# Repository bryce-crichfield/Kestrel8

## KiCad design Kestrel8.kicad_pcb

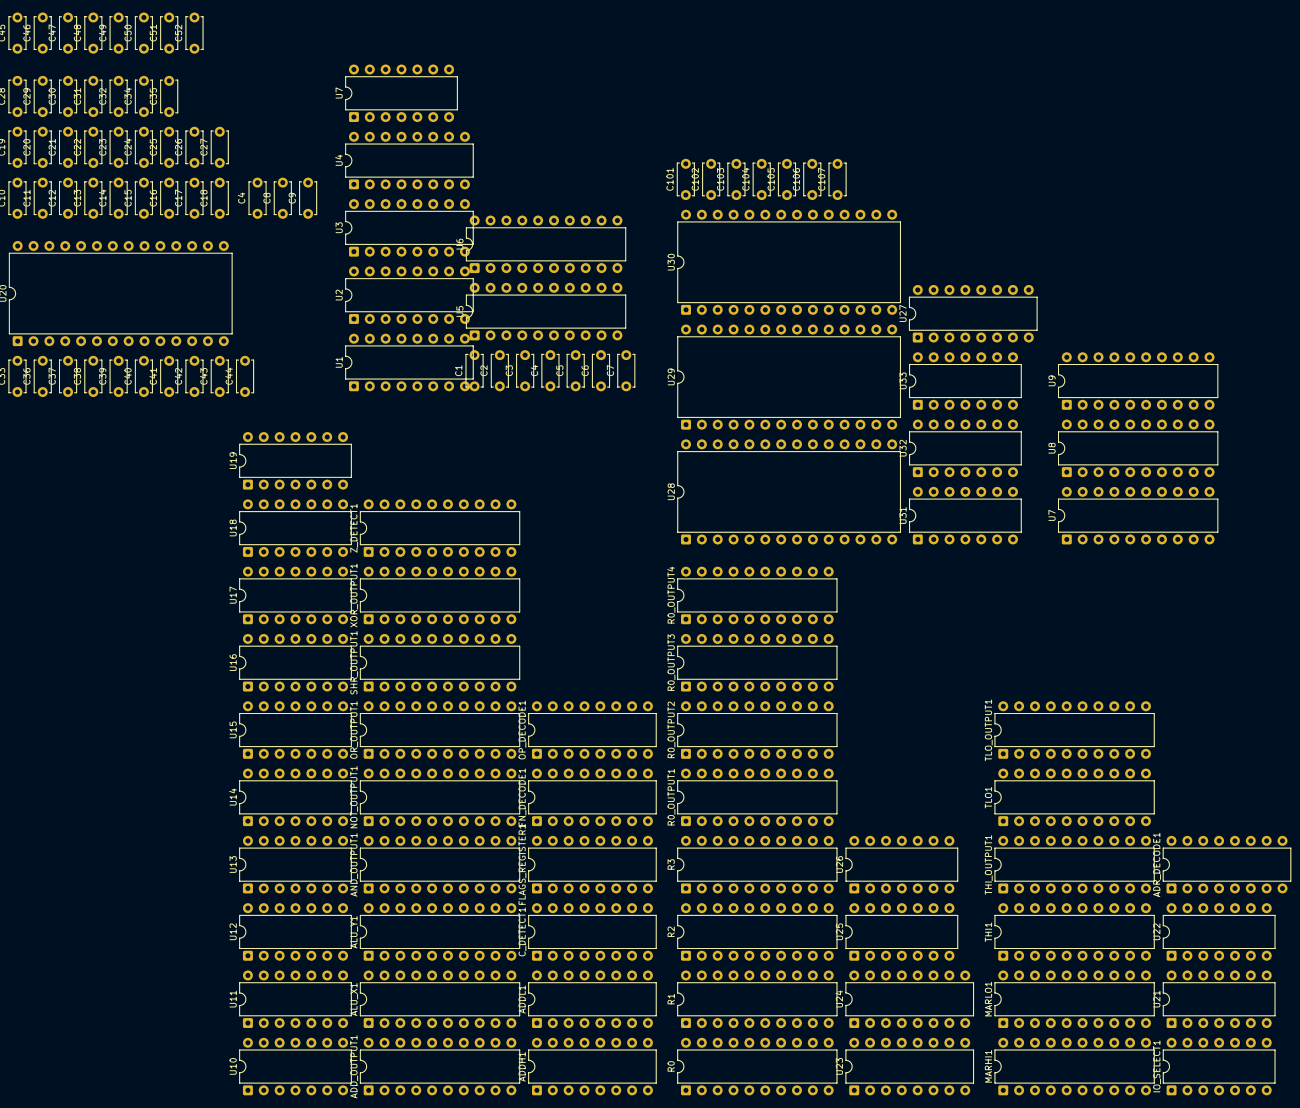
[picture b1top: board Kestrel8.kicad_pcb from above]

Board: 2 copper layers, 125 parts (0 on the bottom side), 249 nets, no tracks yet.

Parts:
ADDH1: 74LS283; DIP-16_W7.62mm
ADDL1: 74LS283; DIP-16_W7.62mm
ADD_OUTPUT1: 74LS541; DIP-20_W7.62mm
ADR_DECODE1: 74LS138; DIP-16_W7.62mm
ALU_X1: 74LS377; DIP-20_W7.62mm
ALU_Y1: 74LS377; DIP-20_W7.62mm
AND_OUTPUT1: 74LS541; DIP-20_W7.62mm
C1, C2, C3, C4, C4#2, C5, C6, C7, C8, C9, C10, C11, C12, C13, C14, C15, C16, C17, C18, C19, C20, C21, C22, C23, C24, C25, C26, C27, C28, C29, C30, C31, C32, C33, C34, C35, C36, C37, C38, C39, C40, C41, C42, C43, C44, C45, C46, C47, C48, C49, C50, C51, C52, C101, C102, C103, C104, C105, C106, C107: 100nF; C_Disc_D5.0mm_W2.5mm_P5.00mm
C_DETECT1: 74HC151; DIP-16_W7.62mm
FLAGS_REGISTER1: 74LS173; DIP-16_W7.62mm
FN_DECODE1: 74LS138; DIP-16_W7.62mm
IO_SELECT1: 74LS30; DIP-14_W7.62mm
MARHI1: 74LS377; DIP-20_W7.62mm
MARLO1: 74LS377; DIP-20_W7.62mm
NOT_OUTPUT1: 74LS540; DIP-20_W7.62mm
OP_DECODE1: 74LS157; DIP-16_W7.62mm
OR_OUTPUT1: 74LS541; DIP-20_W7.62mm
R0, R1, R2, R3: 74LS377; DIP-20_W7.62mm
R0_OUTPUT1, R0_OUTPUT2, R0_OUTPUT3, R0_OUTPUT4: 74LS541; DIP-20_W7.62mm
SHR_OUTPUT1: 74LS541; DIP-20_W7.62mm
THI1: 74LS377; DIP-20_W7.62mm
THI_OUTPUT1: 74HC541; DIP-20_W7.62mm
TLO1: 74LS377; DIP-20_W7.62mm
TLO_OUTPUT1: 74HC541; DIP-20_W7.62mm
U1, U2, U3, U4, U27: 74LS163; DIP-16_W7.62mm
U5, U6, U9: 74LS541; DIP-20_W7.62mm
U7, U8: 74LS377; DIP-20_W7.62mm
U7#2: 74LS04; DIP-14_W7.62mm
U10, U14, U17, U18: 74LS86; DIP-14_W7.62mm
U11: 74HC00; DIP-14_W7.62mm
U12, U15, U25, U31: 74LS08; DIP-14_W7.62mm
U13, U16: 74HC32; DIP-14_W7.62mm
U19: 74LS11; DIP-14_W7.62mm
U20: CY62256-70PC; DIP-28_W15.24mm
U21: 74LS30; DIP-14_W7.62mm
U22, U32: 74LS32; DIP-14_W7.62mm
U23, U24: 74LS139; DIP-16_W7.62mm
U26: 74LS00; DIP-14_W7.62mm
U28, U29, U30: AT28C64B; DIP-28_W15.24mm
U33: 74LS74; DIP-14_W7.62mm
XOR_OUTPUT1: 74LS541; DIP-20_W7.62mm
Z_DETECT1: 74LS688; DIP-20_W7.62mm

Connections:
/ControlUnit/SC_0: U27.14 (Q0), U28.10 (A0), U29.10 (A0), U30.10 (A0)
/ControlUnit/SC_1: U27.13 (Q1), U28.9 (A1), U29.9 (A1), U30.9 (A1)
/ControlUnit/SC_2: U27.12 (Q2), U28.8 (A2), U29.8 (A2), U30.8 (A2)
/ControlUnit/SC_3: U27.11 (Q3), U28.7 (A3), U29.7 (A3), U30.7 (A3)
/ControlUnit//HALT_SET: U32.3, U33.4 (~S)
/ControlUnit//SC_MR: U27.1 (~MR), U31.3
/ProgramCounter/PC_RIPPLE_1: U1.15 (TC), U2.10 (CET)
/ProgramCounter/PC_RIPPLE_2: U2.15 (TC), U3.10 (CET)
/ProgramCounter/PC_RIPPLE_3: U3.15 (TC), U4.10 (CET)
/ProgramCounter/Q_0: U1.14 (Q0), U5.2 (A0)
/ProgramCounter/Q_1: U1.13 (Q1), U5.3 (A1)
/ProgramCounter/Q_2: U1.12 (Q2), U5.4 (A2)
/ProgramCounter/Q_3: U1.11 (Q3), U5.5 (A3)
/ProgramCounter/Q_4: U2.14 (Q0), U5.6 (A4)
/ProgramCounter/Q_5: U2.13 (Q1), U5.7 (A5)
/ProgramCounter/Q_6: U2.12 (Q2), U5.8 (A6)
/ProgramCounter/Q_7: U2.11 (Q3), U5.9 (A7)
/ProgramCounter/Q_8: U3.14 (Q0), U6.2 (A0)
/ProgramCounter/Q_9: U3.13 (Q1), U6.3 (A1)
/ProgramCounter/Q_10: U3.12 (Q2), U6.4 (A2)
/ProgramCounter/Q_11: U3.11 (Q3), U6.5 (A3)
/ProgramCounter/Q_12: U4.14 (Q0), U6.6 (A4)
/ProgramCounter/Q_13: U4.13 (Q1), U6.7 (A5)
/ProgramCounter/Q_14: U4.12 (Q2), U6.8 (A6)
/ProgramCounter/Q_15: U4.11 (Q3), U6.9 (A7)
/RegisterFile/RD_IN: U26.3, U26.4
/RegisterFile//R0_RA: U23.12 (O0), U25.1
/RegisterFile//R0_RB: U24.4 (O0), U25.2
/RegisterFile//R1_RA: U23.11 (O1), U25.4
/RegisterFile//R1_RB: U24.5 (O1), U25.5
/RegisterFile//R2_RA: U23.10 (O2), U25.9
/RegisterFile//R2_RB: U24.6 (O2), U25.10
/RegisterFile//R3_RA: U23.9 (O3), U25.12
/RegisterFile//R3_RB: U24.7 (O3), U25.13
/RegisterFile//RD_IN_GATED: U23.1 (E), U26.6
ADDH_C: ADDH1.9 (C4), C_DETECT1.4 (I0), U11.9, U11.10
ADDL_C: ADDH1.7 (C0), ADDL1.9 (C4)
ADD_0: ADDL1.4 (S1), ADD_OUTPUT1.2 (A0)
ADD_1: ADDL1.1 (S2), ADD_OUTPUT1.3 (A1)
ADD_2: ADDL1.13 (S3), ADD_OUTPUT1.4 (A2)
ADD_3: ADDL1.10 (S4), ADD_OUTPUT1.5 (A3)
ADD_4: ADDH1.4 (S1), ADD_OUTPUT1.6 (A4)
ADD_5: ADDH1.1 (S2), ADD_OUTPUT1.7 (A5)
ADD_6: ADDH1.13 (S3), ADD_OUTPUT1.8 (A6)
ADD_7: ADDH1.10 (S4), ADD_OUTPUT1.9 (A7)
ADR_0: MARLO1.3 (D0), TLO_OUTPUT1.18 (Y0), U1.3 (D0), U5.18 (Y0)
ADR_1: MARLO1.4 (D1), TLO_OUTPUT1.17 (Y1), U1.4 (D1), U5.17 (Y1)
ADR_2: MARLO1.7 (D2), TLO_OUTPUT1.16 (Y2), U1.5 (D2), U5.16 (Y2)
ADR_3: MARLO1.8 (D3), TLO_OUTPUT1.15 (Y3), U1.6 (D3), U5.15 (Y3)
ADR_4: MARLO1.13 (D4), TLO_OUTPUT1.14 (Y4), U2.3 (D0), U5.14 (Y4)
ADR_5: MARLO1.14 (D5), TLO_OUTPUT1.13 (Y5), U2.4 (D1), U5.13 (Y5)
ADR_6: MARLO1.17 (D6), TLO_OUTPUT1.12 (Y6), U2.5 (D2), U5.12 (Y6)
ADR_7: MARLO1.18 (D7), TLO_OUTPUT1.11 (Y7), U2.6 (D3), U5.11 (Y7)
ADR_8: MARHI1.3 (D0), THI_OUTPUT1.18 (Y0), U3.3 (D0), U6.18 (Y0)
ADR_9: MARHI1.4 (D1), THI_OUTPUT1.17 (Y1), U3.4 (D1), U6.17 (Y1)
ADR_10: MARHI1.7 (D2), THI_OUTPUT1.16 (Y2), U3.5 (D2), U6.16 (Y2)
ADR_11: MARHI1.8 (D3), THI_OUTPUT1.15 (Y3), U3.6 (D3), U6.15 (Y3)
ADR_12: MARHI1.13 (D4), THI_OUTPUT1.14 (Y4), U4.3 (D0), U6.14 (Y4)
ADR_13: MARHI1.14 (D5), THI_OUTPUT1.13 (Y5), U4.4 (D1), U6.13 (Y5)
ADR_14: MARHI1.17 (D6), THI_OUTPUT1.12 (Y6), U4.5 (D2), U6.12 (Y6)
ADR_15: MARHI1.18 (D7), THI_OUTPUT1.11 (Y7), U4.6 (D3), U6.11 (Y7)
ALU_FUNC: OP_DECODE1.1 (S), U30.15 (I/O3)
ALU_OP_0: FN_DECODE1.1 (A0), OP_DECODE1.4 (Za)
ALU_OP_1: FN_DECODE1.2 (A1), OP_DECODE1.7 (Zb)
ALU_OP_2: FN_DECODE1.3 (A2), OP_DECODE1.9 (Zc)
AND_0: AND_OUTPUT1.2 (A0), U15.3
AND_1: AND_OUTPUT1.3 (A1), U15.6
AND_2: AND_OUTPUT1.4 (A2), U15.8
AND_3: AND_OUTPUT1.5 (A3), U15.11
AND_4: AND_OUTPUT1.6 (A4), U12.3
AND_5: AND_OUTPUT1.7 (A5), U12.6
AND_6: AND_OUTPUT1.8 (A6), U12.8
AND_7: AND_OUTPUT1.9 (A7), U12.11
CLK: ALU_X1.11 (CP), ALU_Y1.11 (CP), FLAGS_REGISTER1.7 (Cp), MARHI1.11 (CP), MARLO1.11 (CP), R0.11 (CP), R1.11 (CP), R2.11 (CP), R3.11 (CP), THI1.11 (CP), TLO1.11 (CP), U1.2 (CP), U2.2 (CP), U3.2 (CP), U4.2 (CP), U7.11 (CP), U8.11 (CP), U22.2, U27.2 (CP), U32.2
DAT_0: ADD_OUTPUT1.18 (Y0), ALU_X1.3 (D0), ALU_Y1.3 (D0), AND_OUTPUT1.18 (Y0), NOT_OUTPUT1.18 (Y0), OR_OUTPUT1.18 (Y0), R0.3 (D0), R0_OUTPUT1.18 (Y0), R0_OUTPUT2.18 (Y0), R0_OUTPUT3.18 (Y0), R0_OUTPUT4.18 (Y0), R1.3 (D0), R2.3 (D0), R3.3 (D0), SHR_OUTPUT1.18 (Y0), THI1.3 (D0), TLO1.3 (D0), U7.3 (D0), U8.3 (D0), U9.18 (Y0), U20.11 (Q0), XOR_OUTPUT1.18 (Y0), Z_DETECT1.2 (P0)
DAT_1: ADD_OUTPUT1.17 (Y1), ALU_X1.4 (D1), ALU_Y1.4 (D1), AND_OUTPUT1.17 (Y1), NOT_OUTPUT1.17 (Y1), OR_OUTPUT1.17 (Y1), R0.4 (D1), R0_OUTPUT1.17 (Y1), R0_OUTPUT2.17 (Y1), R0_OUTPUT3.17 (Y1), R0_OUTPUT4.17 (Y1), R1.4 (D1), R2.4 (D1), R3.4 (D1), SHR_OUTPUT1.17 (Y1), THI1.4 (D1), TLO1.4 (D1), U7.4 (D1), U8.4 (D1), U9.17 (Y1), U20.12 (Q1), XOR_OUTPUT1.17 (Y1), Z_DETECT1.4 (P1)
DAT_2: ADD_OUTPUT1.16 (Y2), ALU_X1.7 (D2), ALU_Y1.7 (D2), AND_OUTPUT1.16 (Y2), NOT_OUTPUT1.16 (Y2), OR_OUTPUT1.16 (Y2), R0.7 (D2), R0_OUTPUT1.16 (Y2), R0_OUTPUT2.16 (Y2), R0_OUTPUT3.16 (Y2), R0_OUTPUT4.16 (Y2), R1.7 (D2), R2.7 (D2), R3.7 (D2), SHR_OUTPUT1.16 (Y2), THI1.7 (D2), TLO1.7 (D2), U7.7 (D2), U8.7 (D2), U9.16 (Y2), U20.13 (Q2), XOR_OUTPUT1.16 (Y2), Z_DETECT1.6 (P2)
DAT_3: ADD_OUTPUT1.15 (Y3), ALU_X1.8 (D3), ALU_Y1.8 (D3), AND_OUTPUT1.15 (Y3), NOT_OUTPUT1.15 (Y3), OR_OUTPUT1.15 (Y3), R0.8 (D3), R0_OUTPUT1.15 (Y3), R0_OUTPUT2.15 (Y3), R0_OUTPUT3.15 (Y3), R0_OUTPUT4.15 (Y3), R1.8 (D3), R2.8 (D3), R3.8 (D3), SHR_OUTPUT1.15 (Y3), THI1.8 (D3), TLO1.8 (D3), U7.8 (D3), U8.8 (D3), U9.15 (Y3), U20.15 (Q3), XOR_OUTPUT1.15 (Y3), Z_DETECT1.8 (P3)
DAT_4: ADD_OUTPUT1.14 (Y4), ALU_X1.13 (D4), ALU_Y1.13 (D4), AND_OUTPUT1.14 (Y4), NOT_OUTPUT1.14 (Y4), OR_OUTPUT1.14 (Y4), R0.13 (D4), R0_OUTPUT1.14 (Y4), R0_OUTPUT2.14 (Y4), R0_OUTPUT3.14 (Y4), R0_OUTPUT4.14 (Y4), R1.13 (D4), R2.13 (D4), R3.13 (D4), SHR_OUTPUT1.14 (Y4), THI1.13 (D4), TLO1.13 (D4), U7.13 (D4), U8.13 (D4), U9.14 (Y4), U20.16 (Q4), XOR_OUTPUT1.14 (Y4), Z_DETECT1.11 (P4)
DAT_5: ADD_OUTPUT1.13 (Y5), ALU_X1.14 (D5), ALU_Y1.14 (D5), AND_OUTPUT1.13 (Y5), NOT_OUTPUT1.13 (Y5), OR_OUTPUT1.13 (Y5), R0.14 (D5), R0_OUTPUT1.13 (Y5), R0_OUTPUT2.13 (Y5), R0_OUTPUT3.13 (Y5), R0_OUTPUT4.13 (Y5), R1.14 (D5), R2.14 (D5), R3.14 (D5), SHR_OUTPUT1.13 (Y5), THI1.14 (D5), TLO1.14 (D5), U7.14 (D5), U8.14 (D5), U9.13 (Y5), U20.17 (Q5), XOR_OUTPUT1.13 (Y5), Z_DETECT1.13 (P5)
DAT_6: ADD_OUTPUT1.12 (Y6), ALU_X1.17 (D6), ALU_Y1.17 (D6), AND_OUTPUT1.12 (Y6), NOT_OUTPUT1.12 (Y6), OR_OUTPUT1.12 (Y6), R0.17 (D6), R0_OUTPUT1.12 (Y6), R0_OUTPUT2.12 (Y6), R0_OUTPUT3.12 (Y6), R0_OUTPUT4.12 (Y6), R1.17 (D6), R2.17 (D6), R3.17 (D6), SHR_OUTPUT1.12 (Y6), THI1.17 (D6), TLO1.17 (D6), U7.17 (D6), U8.17 (D6), U9.12 (Y6), U20.18 (Q6), XOR_OUTPUT1.12 (Y6), Z_DETECT1.15 (P6)
DAT_7: ADD_OUTPUT1.11 (Y7), ALU_X1.18 (D7), ALU_Y1.18 (D7), AND_OUTPUT1.11 (Y7), NOT_OUTPUT1.11 (Y7), OR_OUTPUT1.11 (Y7), R0.18 (D7), R0_OUTPUT1.11 (Y7), R0_OUTPUT2.11 (Y7), R0_OUTPUT3.11 (Y7), R0_OUTPUT4.11 (Y7), R1.18 (D7), R2.18 (D7), R3.18 (D7), SHR_OUTPUT1.11 (Y7), THI1.18 (D7), TLO1.18 (D7), U7.18 (D7), U8.18 (D7), U9.11 (Y7), U20.19 (Q7), XOR_OUTPUT1.11 (Y7), Z_DETECT1.17 (P7)
GND: ADDH1.8 (GND), ADDL1.8 (GND), ADD_OUTPUT1.1 (G1), ADD_OUTPUT1.10 (GND), ADR_DECODE1.5 (E2), ADR_DECODE1.8 (GND), ALU_X1.10 (GND), ALU_Y1.10 (GND), AND_OUTPUT1.1 (G1), AND_OUTPUT1.10 (GND), C1.2, C2.2, C3.2, C4.2, C4#2.2, C5.2, C6.2, C7.2, C8.2, C9.2, C10.2, C11.2, C12.2, C13.2, C14.2, C15.2, C16.2, C17.2, C18.2, C19.2, C20.2, C21.2, C22.2, C23.2, C24.2, C25.2, C26.2, C27.2, C28.2, C29.2, C30.2, C31.2, C32.2, C33.2, C34.2, C35.2, C36.2, C37.2, C38.2, C39.2, C40.2, C41.2, C42.2, C43.2, C44.2, C45.2, C46.2, C47.2, C48.2, C49.2, C50.2, C51.2, C52.2, C101.2, C102.2, C103.2, C104.2, C105.2, C106.2, C107.2, C_DETECT1.1 (I3), C_DETECT1.2 (I2), C_DETECT1.7 (~E), C_DETECT1.8 (GND), C_DETECT1.14 (I5), C_DETECT1.15 (I4), FLAGS_REGISTER1.1 (Oe1), FLAGS_REGISTER1.2 (Oe2), FLAGS_REGISTER1.8 (GND), FLAGS_REGISTER1.10 (E2), FLAGS_REGISTER1.11 (D3), FLAGS_REGISTER1.12 (D2), FN_DECODE1.5 (E2), FN_DECODE1.8 (GND), MARLO1.10 (GND), NOT_OUTPUT1.1 (G1), NOT_OUTPUT1.10 (GND), OP_DECODE1.2 (I0a), OP_DECODE1.5 (I0b), OP_DECODE1.8 (GND), OP_DECODE1.11 (I0c), OP_DECODE1.13 (I1d), OP_DECODE1.14 (I0d), OP_DECODE1.15 (E), OR_OUTPUT1.1 (G1), OR_OUTPUT1.10 (GND), R0.10 (GND), R0_OUTPUT1.1 (G1), R0_OUTPUT1.10 (GND), R0_OUTPUT2.1 (G1), R0_OUTPUT2.10 (GND), R0_OUTPUT3.1 (G1), R0_OUTPUT3.10 (GND), R0_OUTPUT4.1 (G1), R0_OUTPUT4.10 (GND), R1.10 (GND), R2.10 (GND), R3.10 (GND), SHR_OUTPUT1.1 (G1), SHR_OUTPUT1.9 (A7), SHR_OUTPUT1.10 (GND), THI1.10 (GND), THI_OUTPUT1.10 (GND), TLO1.10 (GND), TLO_OUTPUT1.10 (GND), U1.8 (GND), U2.8 (GND), U3.8 (GND), U4.8 (GND), U5.1 (G1), U5.10 (GND), U6.1 (G1), U6.10 (GND), U7.10 (GND), U7#2.7 (GND), U8.10 (GND), U9.1 (G1), U9.10 (GND), U10.7 (GND), U11.7 (GND), U12.7 (GND), U13.7 (GND), U14.7 (GND), U15.7 (GND), U16.7 (GND), U17.7 (GND), U18.7 (GND), U19.3, U19.4, U19.5, U19.7 (GND), U19.9, U19.10, U19.11, U20.14 (GND), U21.7 (GND), U22.4, U22.5, U22.7 (GND), U22.9, U22.10, U22.12, U22.13, U23.8 (GND), U24.8 (GND), U24.13 (A1), U24.14 (A0), U25.7 (GND), U26.7 (GND), U26.9, U26.10, U26.12, U26.13, U27.3 (D0), U27.4 (D1), U27.5 (D2), U27.6 (D3), U27.8 (GND), U28.2 (A12), U28.14 (GND), U28.20 (~CE), U28.21 (A10), U28.22 (~OE), U28.23 (A11), U29.2 (A12), U29.14 (GND), U29.20 (~CE), U29.21 (A10), U29.22 (~OE), U29.23 (A11), U30.2 (A12), U30.14 (GND), U30.20 (~CE), U30.21 (A10), U30.22 (~OE), U30.23 (A11), U31.4, U31.5, U31.7 (GND), U31.9, U31.10, U31.12, U31.13, U32.4, U32.5, U32.7 (GND), U32.9, U32.10, U32.12, U32.13, U33.2 (D), U33.3 (C), U33.7 (GND), U33.11 (C), U33.12 (D), XOR_OUTPUT1.1 (G1), XOR_OUTPUT1.10 (GND), Z_DETECT1.1 (G), Z_DETECT1.3 (R0), Z_DETECT1.5 (R1), Z_DETECT1.7 (R2), Z_DETECT1.9 (R3), Z_DETECT1.10 (GND), Z_DETECT1.12 (R4), Z_DETECT1.14 (R5), Z_DETECT1.16 (R6), Z_DETECT1.18 (R7)
IR0_4: U7.12 (Q4), U28.4 (A6), U29.4 (A6), U30.4 (A6)
IR0_5: U7.15 (Q5), U28.3 (A7), U29.3 (A7), U30.3 (A7)
IR0_6: U7.16 (Q6), U28.25 (A8), U29.25 (A8), U30.25 (A8)
IR0_7: U7.19 (Q7), U28.24 (A9), U29.24 (A9), U30.24 (A9)
IR1_0: OP_DECODE1.3 (I1a), U8.2 (Q0), U9.2 (A0)
IR1_1: OP_DECODE1.6 (I1b), U8.5 (Q1), U9.3 (A1)
IR1_2: OP_DECODE1.10 (I1c), U8.6 (Q2), U9.4 (A2)
IR1_3: U8.9 (Q3), U9.5 (A3)
IR1_4: U8.12 (Q4), U9.6 (A4)
IR1_5: U8.15 (Q5), U9.7 (A5)
IR1_6: U8.16 (Q6), U9.8 (A6)
IR1_7: U8.19 (Q7), U9.9 (A7)
MA_0: MARLO1.2 (Q0), U20.10 (A0)
MA_1: MARLO1.5 (Q1), U20.9 (A1)
MA_2: MARLO1.6 (Q2), U20.8 (A2)
MA_3: MARLO1.9 (Q3), U20.7 (A3)
MA_4: ADR_DECODE1.1 (A0), MARLO1.12 (Q4), U20.6 (A4)
MA_5: ADR_DECODE1.2 (A1), MARLO1.15 (Q5), U20.5 (A5)
MA_6: ADR_DECODE1.3 (A2), MARLO1.16 (Q6), U20.4 (A6)
MA_7: MARLO1.19 (Q7), U20.3 (A7)
MA_8: IO_SELECT1.1, MARHI1.2 (Q0), U20.25 (A8)
MA_9: IO_SELECT1.2, MARHI1.5 (Q1), U20.24 (A9)
MA_10: IO_SELECT1.3, MARHI1.6 (Q2), U20.21 (A10)
MA_11: IO_SELECT1.4, MARHI1.9 (Q3), U20.23 (A11)
MA_12: IO_SELECT1.5, MARHI1.12 (Q4), U20.2 (A12)
MA_13: IO_SELECT1.6, MARHI1.15 (Q5), U20.26 (A13)
MA_14: IO_SELECT1.11, MARHI1.16 (Q6), U20.1 (A14)
MA_15: IO_SELECT1.12, MARHI1.19 (Q7), U20.20 (~CS)
unnamed: R0.2 (Q0), R0_OUTPUT4.2 (A0)
unnamed: R0.5 (Q1), R0_OUTPUT4.3 (A1)
unnamed: R0.6 (Q2), R0_OUTPUT4.4 (A2)
unnamed: R0.9 (Q3), R0_OUTPUT4.5 (A3)
unnamed: R0.12 (Q4), R0_OUTPUT4.6 (A4)
unnamed: R0.15 (Q5), R0_OUTPUT4.7 (A5)
unnamed: R0.16 (Q6), R0_OUTPUT4.8 (A6)
unnamed: R0.19 (Q7), R0_OUTPUT4.9 (A7)
unnamed: R0_OUTPUT1.2 (A0), R1.2 (Q0)
unnamed: R0_OUTPUT1.3 (A1), R1.5 (Q1)
unnamed: R0_OUTPUT1.4 (A2), R1.6 (Q2)
unnamed: R0_OUTPUT1.5 (A3), R1.9 (Q3)
unnamed: R0_OUTPUT1.6 (A4), R1.12 (Q4)
unnamed: R0_OUTPUT1.7 (A5), R1.15 (Q5)
unnamed: R0_OUTPUT1.8 (A6), R1.16 (Q6)
unnamed: R0_OUTPUT1.9 (A7), R1.19 (Q7)
unnamed: R0_OUTPUT2.2 (A0), R2.2 (Q0)
unnamed: R0_OUTPUT2.3 (A1), R2.5 (Q1)
unnamed: R0_OUTPUT2.4 (A2), R2.6 (Q2)
unnamed: R0_OUTPUT2.5 (A3), R2.9 (Q3)
unnamed: R0_OUTPUT2.6 (A4), R2.12 (Q4)
unnamed: R0_OUTPUT2.7 (A5), R2.15 (Q5)
unnamed: R0_OUTPUT2.8 (A6), R2.16 (Q6)
unnamed: R0_OUTPUT2.9 (A7), R2.19 (Q7)
unnamed: R0_OUTPUT3.2 (A0), R3.2 (Q0)
unnamed: R0_OUTPUT3.3 (A1), R3.5 (Q1)
unnamed: R0_OUTPUT3.4 (A2), R3.6 (Q2)
unnamed: R0_OUTPUT3.5 (A3), R3.9 (Q3)
unnamed: R0_OUTPUT3.6 (A4), R3.12 (Q4)
unnamed: R0_OUTPUT3.7 (A5), R3.15 (Q5)
unnamed: R0_OUTPUT3.8 (A6), R3.16 (Q6)
unnamed: R0_OUTPUT3.9 (A7), R3.19 (Q7)
OR_0: OR_OUTPUT1.2 (A0), U16.3
OR_1: OR_OUTPUT1.3 (A1), U16.6
OR_2: OR_OUTPUT1.4 (A2), U16.8
OR_3: OR_OUTPUT1.5 (A3), U16.11
OR_4: OR_OUTPUT1.6 (A4), U13.3
OR_5: OR_OUTPUT1.7 (A5), U13.6
OR_6: OR_OUTPUT1.8 (A6), U13.8
OR_7: OR_OUTPUT1.9 (A7), U13.11
PC_IN: U7#2.1, U7#2.3, U7#2.5, U7#2.9
PC_INC: U1.7 (CEP), U1.10 (CET), U2.7 (CEP), U3.7 (CEP), U4.7 (CEP), U28.13 (I/O2)
PC_OUT: U7#2.11, U7#2.13
RESET: U11.4, U11.5
SUB: ADDL1.7 (C0), U10.2, U10.5, U10.10, U10.13, U11.11, U18.2, U18.5, U18.10, U18.13
SUB_0: ADDL1.6 (B1), U10.3
SUB_1: ADDL1.2 (B2), U10.6
SUB_2: ADDL1.15 (B3), U10.8
SUB_3: ADDL1.11 (B4), U10.11
SUB_4: ADDH1.6 (B1), U18.3
SUB_5: ADDH1.2 (B2), U18.6
SUB_6: ADDH1.15 (B3), U18.8
SUB_7: ADDH1.11 (B4), U18.11
THI_0: THI1.2 (Q0), THI_OUTPUT1.2 (A0)
THI_1: THI1.5 (Q1), THI_OUTPUT1.3 (A1)
THI_2: THI1.6 (Q2), THI_OUTPUT1.4 (A2)
THI_3: THI1.9 (Q3), THI_OUTPUT1.5 (A3)
THI_4: THI1.12 (Q4), THI_OUTPUT1.6 (A4)
THI_5: THI1.15 (Q5), THI_OUTPUT1.7 (A5)
THI_6: THI1.16 (Q6), THI_OUTPUT1.8 (A6)
THI_7: THI1.19 (Q7), THI_OUTPUT1.9 (A7)
TLO_0: TLO1.2 (Q0), TLO_OUTPUT1.2 (A0)
TLO_1: TLO1.5 (Q1), TLO_OUTPUT1.3 (A1)
TLO_2: TLO1.6 (Q2), TLO_OUTPUT1.4 (A2)
TLO_3: TLO1.9 (Q3), TLO_OUTPUT1.5 (A3)
TLO_4: TLO1.12 (Q4), TLO_OUTPUT1.6 (A4)
TLO_5: TLO1.15 (Q5), TLO_OUTPUT1.7 (A5)
TLO_6: TLO1.16 (Q6), TLO_OUTPUT1.8 (A6)
TLO_7: TLO1.19 (Q7), TLO_OUTPUT1.9 (A7)
VCC: ADDH1.16 (VCC), ADDL1.16 (VCC), ADD_OUTPUT1.20 (VCC), ADR_DECODE1.6 (E3), ADR_DECODE1.16 (VCC), ALU_X1.20 (VCC), ALU_Y1.20 (VCC), AND_OUTPUT1.20 (VCC), C1.1, C2.1, C3.1, C4.1, C4#2.1, C5.1, C6.1, C7.1, C8.1, C9.1, C10.1, C11.1, C12.1, C13.1, C14.1, C15.1, C16.1, C17.1, C18.1, C19.1, C20.1, C21.1, C22.1, C23.1, C24.1, C25.1, C26.1, C27.1, C28.1, C29.1, C30.1, C31.1, C32.1, C33.1, C34.1, C35.1, C36.1, C37.1, C38.1, C39.1, C40.1, C41.1, C42.1, C43.1, C44.1, C45.1, C46.1, C47.1, C48.1, C49.1, C50.1, C51.1, C52.1, C101.1, C102.1, C103.1, C104.1, C105.1, C106.1, C107.1, C_DETECT1.16 (VCC), FLAGS_REGISTER1.16 (VCC), FN_DECODE1.6 (E3), FN_DECODE1.16 (VCC), MARHI1.20 (VCC), MARLO1.20 (VCC), NOT_OUTPUT1.20 (VCC), OP_DECODE1.16 (VCC), OR_OUTPUT1.20 (VCC), R0.20 (VCC), R0_OUTPUT1.20 (VCC), R0_OUTPUT2.20 (VCC), R0_OUTPUT3.20 (VCC), R0_OUTPUT4.20 (VCC), R1.20 (VCC), R2.20 (VCC), R3.20 (VCC), SHR_OUTPUT1.20 (VCC), THI1.20 (VCC), THI_OUTPUT1.20 (VCC), TLO1.20 (VCC), TLO_OUTPUT1.20 (VCC), U1.16 (VCC), U2.16 (VCC), U3.16 (VCC), U4.16 (VCC), U5.20 (VCC), U6.20 (VCC), U7.20 (VCC), U7#2.14 (VCC), U8.20 (VCC), U9.20 (VCC), U10.14 (VCC), U11.1, U11.2, U11.14 (VCC), U12.14 (VCC), U13.14 (VCC), U14.14 (VCC), U15.14 (VCC), U16.14 (VCC), U17.14 (VCC), U18.14 (VCC), U19.14 (VCC), U20.28 (VCC), U21.14 (VCC), U22.14 (VCC), U23.16 (VCC), U24.15 (E), U24.16 (VCC), U25.14 (VCC), U26.14 (VCC), U27.7 (CEP), U27.9 (~PE), U27.10 (CET), U27.16 (VCC), U28.27 (~WE), U28.28 (VCC), U29.27 (~WE), U29.28 (VCC), U30.27 (~WE), U30.28 (VCC), U31.14 (VCC), U32.14 (VCC), U33.10 (~S), U33.13 (~R), U33.14 (VCC), XOR_OUTPUT1.20 (VCC), Z_DETECT1.20 (VCC)
XOR_0: U14.3, XOR_OUTPUT1.2 (A0)
XOR_1: U14.6, XOR_OUTPUT1.3 (A1)
XOR_2: U14.8, XOR_OUTPUT1.4 (A2)
XOR_3: U14.11, XOR_OUTPUT1.5 (A3)
XOR_4: U17.3, XOR_OUTPUT1.6 (A4)
XOR_5: U17.6, XOR_OUTPUT1.7 (A5)
XOR_6: U17.8, XOR_OUTPUT1.8 (A6)
XOR_7: U17.11, XOR_OUTPUT1.9 (A7)
X_0: ADDL1.5 (A1), ALU_X1.2 (Q0), C_DETECT1.13 (I6), NOT_OUTPUT1.2 (A0), U14.1, U15.1, U16.1
X_1: ADDL1.3 (A2), ALU_X1.5 (Q1), NOT_OUTPUT1.3 (A1), SHR_OUTPUT1.2 (A0), U14.4, U15.4, U16.4
X_2: ADDL1.14 (A3), ALU_X1.6 (Q2), NOT_OUTPUT1.4 (A2), SHR_OUTPUT1.3 (A1), U14.9, U15.9, U16.9
X_3: ADDL1.12 (A4), ALU_X1.9 (Q3), NOT_OUTPUT1.5 (A3), SHR_OUTPUT1.4 (A2), U14.12, U15.12, U16.12
X_4: ADDH1.5 (A1), ALU_X1.12 (Q4), NOT_OUTPUT1.6 (A4), SHR_OUTPUT1.5 (A3), U12.1, U13.1, U17.1
X_5: ADDH1.3 (A2), ALU_X1.15 (Q5), NOT_OUTPUT1.7 (A5), SHR_OUTPUT1.6 (A4), U12.4, U13.4, U17.4
X_6: ADDH1.14 (A3), ALU_X1.16 (Q6), NOT_OUTPUT1.8 (A6), SHR_OUTPUT1.7 (A5), U12.9, U13.9, U17.9
X_7: ADDH1.12 (A4), ALU_X1.19 (Q7), NOT_OUTPUT1.9 (A7), SHR_OUTPUT1.8 (A6), U12.12, U13.12, U17.12
Y_0: ALU_Y1.2 (Q0), U10.1, U14.2, U15.2, U16.2
Y_1: ALU_Y1.5 (Q1), U10.4, U14.5, U15.5, U16.5
Y_2: ALU_Y1.6 (Q2), U10.9, U14.10, U15.10, U16.10
Y_3: ALU_Y1.9 (Q3), U10.12, U14.13, U15.13, U16.13
Y_4: ALU_Y1.12 (Q4), U12.2, U13.2, U17.2, U18.1
Y_5: ALU_Y1.15 (Q5), U12.5, U13.5, U17.5, U18.4
Y_6: ALU_Y1.16 (Q6), U12.10, U13.10, U17.10, U18.9
Y_7: ALU_Y1.19 (Q7), U12.13, U13.13, U17.13, U18.12
/ADDH_C: C_DETECT1.3 (I1), C_DETECT1.12 (I7), U11.8
/ADD_OUT: ADD_OUTPUT1.19 (G2), U19.12
/ALU_OUT: FN_DECODE1.4 (E1), U30.13 (I/O2)
/AND_OUT: AND_OUTPUT1.19 (G2), FN_DECODE1.13 (O2)
/C: FLAGS_REGISTER1.3 (Q0), U28.6 (A4), U29.6 (A4), U30.6 (A4)
/CARRY: C_DETECT1.6 (~Y), FLAGS_REGISTER1.14 (D0)
/F_IN: FLAGS_REGISTER1.9 (E1), U30.16 (I/O4)
/HALT: U30.18 (I/O6), U32.1
/IO_SEL: ADR_DECODE1.4 (E1), IO_SELECT1.8
/IR0_IN: U7.1 (~E), U29.12 (I/O1)
/IR1_IN: U8.1 (~E), U29.13 (I/O2)
/IR1_OUT: U9.19 (G2), U29.15 (I/O3)
/MAR_IN: MARHI1.1 (~E), MARLO1.1 (~E), U28.15 (I/O3)
/NOT_OUT: FN_DECODE1.10 (O5), NOT_OUTPUT1.19 (G2)
/OR_OUT: FN_DECODE1.12 (O3), OR_OUTPUT1.19 (G2)
/PC_IN: U1.9 (~PE), U2.9 (~PE), U3.9 (~PE), U4.9 (~PE), U28.12 (I/O1)
/PC_OUT: U5.19 (G2), U6.19 (G2), U28.11 (I/O0)
/R0_IN: R0.1 (~E), U23.4 (O0)
/R0_OUT: R0_OUTPUT4.19 (G2), U25.3
/R1_IN: R1.1 (~E), U23.5 (O1)
/R1_OUT: R0_OUTPUT1.19 (G2), U25.6
/R2_IN: R2.1 (~E), U23.6 (O2)
/R2_OUT: R0_OUTPUT2.19 (G2), U25.8
/R3_IN: R3.1 (~E), U23.7 (O3)
/R3_OUT: R0_OUTPUT3.19 (G2), U25.11
/RAM_IN: U22.1, U29.11 (I/O0)
/RAM_OUT: U20.22 (~OE), U28.19 (I/O7)
/RAM_WE: U20.27 (~WE), U22.3
/RA_OUT: U23.15 (E), U29.18 (I/O6)
/RB_OUT: U24.1 (E), U29.19 (I/O7)
/RD_IN: U26.1, U26.2, U29.16 (I/O4)
/RESET: FLAGS_REGISTER1.15 (Mr), U1.1 (~MR), U2.1 (~MR), U3.1 (~MR), U4.1 (~MR), U11.6, U31.2, U33.1 (~R)
/SC_CLR: U30.17 (I/O5), U31.1
/SEL_ADD: FN_DECODE1.15 (O0), U19.1
/SEL_CMP: FN_DECODE1.7 (O7), U11.13, U19.13, U26.5
/SEL_SUB: FN_DECODE1.14 (O1), U11.12, U19.2
/THI_IN: THI1.1 (~E), U28.17 (I/O5)
/TLO_IN: TLO1.1 (~E), U28.16 (I/O4)
/T_OUT: THI_OUTPUT1.19 (~OE2), TLO_OUTPUT1.19 (~OE2), U28.18 (I/O6)
/XOR_OUT: FN_DECODE1.11 (O4), XOR_OUTPUT1.19 (G2)
/X_IN: ALU_X1.1 (~E), U30.11 (I/O0)
/Y_IN: ALU_Y1.1 (~E), U30.12 (I/O1)
/Z: FLAGS_REGISTER1.4 (Q1), U28.5 (A5), U29.5 (A5), U30.5 (A5)
/ZERO: FLAGS_REGISTER1.13 (D1), Z_DETECT1.19 (P=R)
